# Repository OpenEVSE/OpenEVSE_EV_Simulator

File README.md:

# OpenEVSE_EV_Simulator
OpenEVSE EV Simulator

OpenEVSE_EVSIM_V1 Original version - Jumpers

OpenEVSE_EVSIM_V2 DIP switches - additave parralel resistors

See the [build guide](https://openevse.dozuki.com/Guide/How+to+Build+OpenEVSE+EV+Simulator+v2/6#s28) and [testing guide](https://openevse.dozuki.com/Guide/Testing+Basic+and+Advanced/12#s78) for more info.

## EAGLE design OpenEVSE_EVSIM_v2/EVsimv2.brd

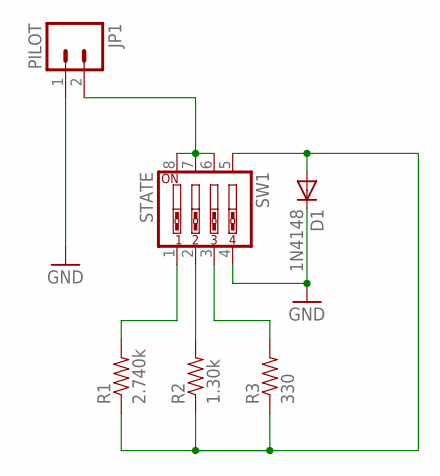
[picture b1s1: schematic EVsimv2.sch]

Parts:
D1: 1N4148; DIODE-1N4148
JP1: PILOT; SCREWTERMINAL-3.5MM-2_LOCK
R1: 2.740k; AXIAL-0.4
R2: 1.30k; AXIAL-0.4
R3: 330; AXIAL-0.4
SW1: STATE; EDG-04

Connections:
GND: D1.C, JP1.1, SW1.4
unnamed: D1.A, R1.P$1 (1), R2.P$1 (1), R3.P$1 (1), SW1.5
unnamed: JP1.2, SW1.6, SW1.7, SW1.8
unnamed: R1.P$2 (2), SW1.1
unnamed: R2.P$2 (2), SW1.2
unnamed: R3.P$2 (2), SW1.3

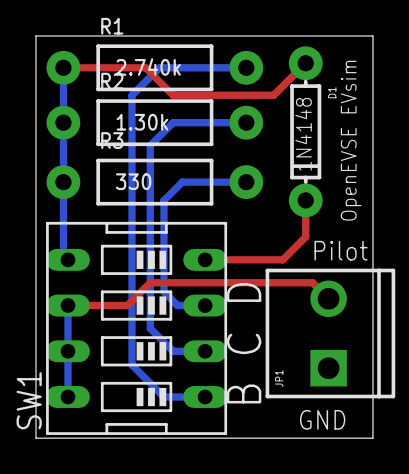
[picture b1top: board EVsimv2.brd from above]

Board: 2 copper layers, 18.7 x 22.3 mm, 6 parts (0 on the bottom side), 6 nets.

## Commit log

2015-10-09 :tada: Added .gitattributes & .gitignore files
2015-10-09 OpenEVSE EV Simulator
    OpenEVSE EV Simulator
2017-07-20 Added links to useful docs
